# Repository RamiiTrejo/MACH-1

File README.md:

# Mach-1
Proyecto de robot seguidor de línea de alta velocidad, orientado a competencias de Line Follower Racing (LNR). Está diseñado para la categoría profesional, incorporando soluciones avanzadas como un sistema de succión que mejora la adherencia y el rendimiento en pista.

# Objetivos
Desarrollar un vehículo autónomo capaz de detectar y seguir una trayectoria con alta precisión y velocidad, optimizando tanto el hardware como el software para lograr un desempeño competitivo.

# Componentes
- ATMEGA238P, AU
- TA6586
- MOTOR CORELESS 8520
- TURBINA CON MOTOR CORELESS 716
- REGLETA QTR8A
- BATERÍA 2 350mAh~450mAh

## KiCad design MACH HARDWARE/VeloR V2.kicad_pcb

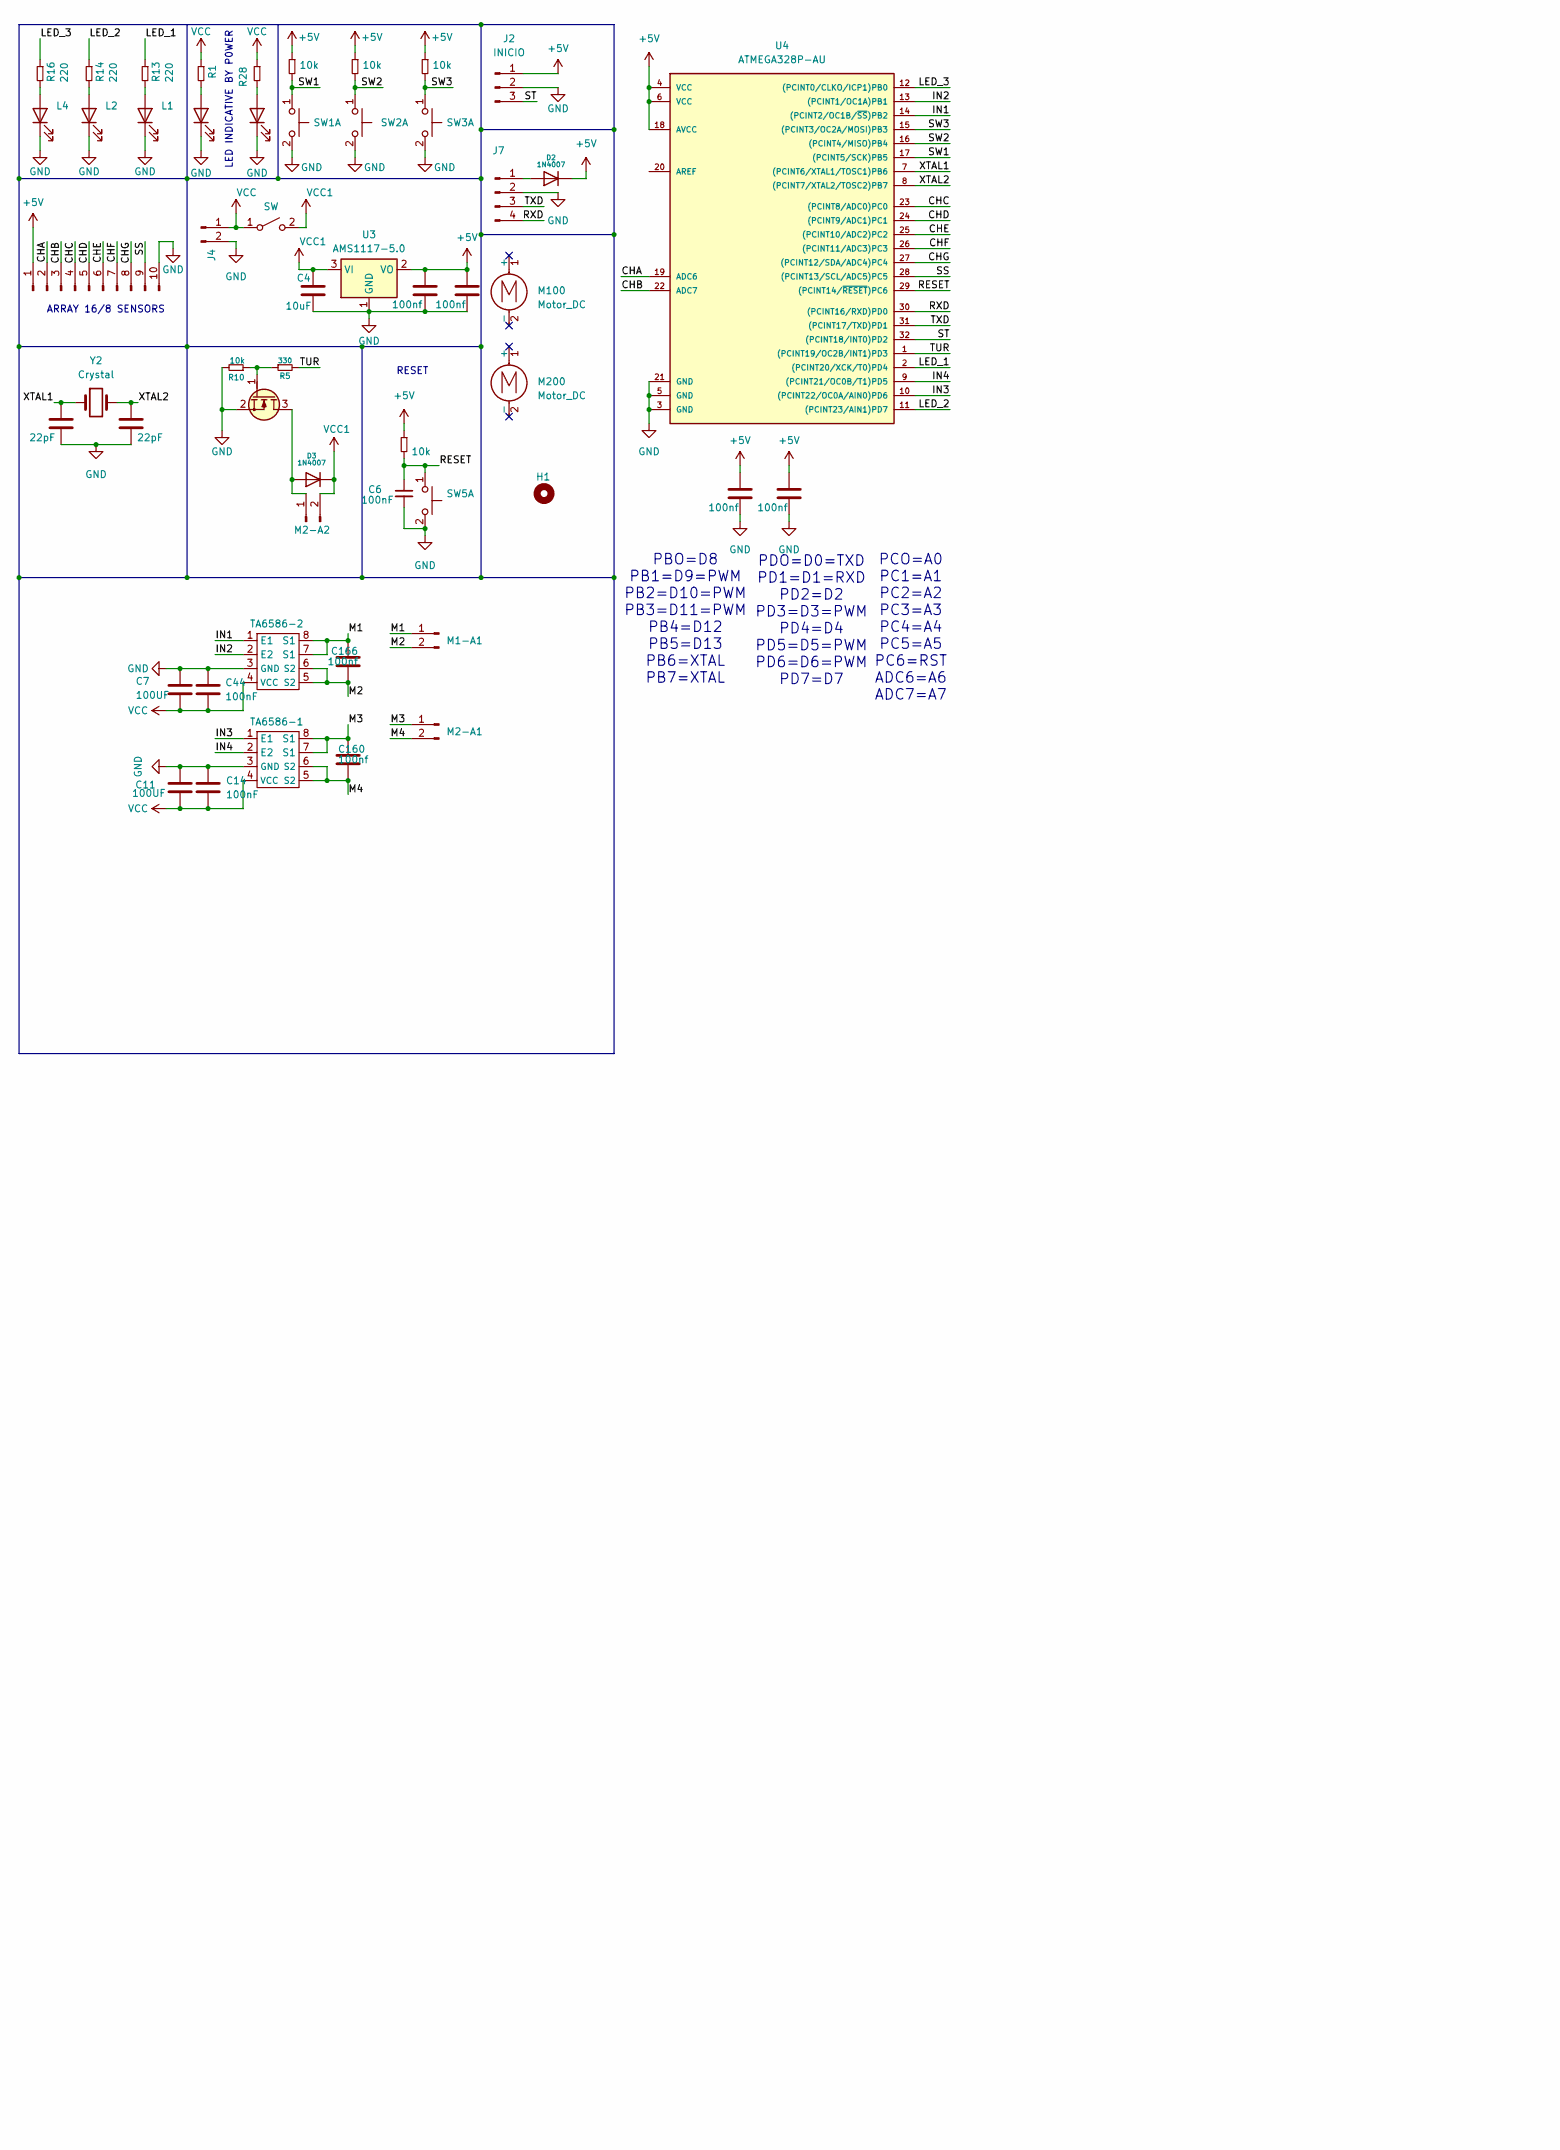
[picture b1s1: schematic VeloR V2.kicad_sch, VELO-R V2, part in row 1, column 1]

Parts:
C1, C2, C3, C15, C160, C166: 100nf; C_0805_2012Metric_Pad1.18x1.45mm_HandSolder
C4: 10uF; C_1206_3216Metric_Pad1.33x1.80mm_HandSolder
C5, C9: 22pF; C_0805_2012Metric_Pad1.18x1.45mm_HandSolder
C6, C14, C44: 100nF; C_0805_2012Metric_Pad1.18x1.45mm_HandSolder
C7, C11: 100UF; CP_EIA-7343-20_Kemet-V
D1, D11: LED; LED_0805_2012Metric_Pad1.15x1.40mm_HandSolder
D2, D3: 1N4007; D_SMA
H1: MountingHole; TURBINA
J2: INICIO; PinHeader_1x03_P2.54mm_Vertical
J3: Conn_01x10_Pin; JST_XH_S10B-XH-A_1x10_P2.50mm_Horizontal
J4: Conn_01x02_Pin; JST_XH_B3B-XH-A_1x03_P2.50mm_Vertical
J7: Conn_01x04_Pin; PinHeader_1x04_P2.54mm_Horizontal
L1, L2, L4: LED; LED_0805_2012Metric_Pad1.15x1.40mm_HandSolder
M1-A1, M2-A1, M2-A2: Conn_01x02_Pin; Hirose_DF13-02P-1.25DSA_1x02_P1.25mm_Vertical
M100, M200: Motor_DC; Coreless motor
Q1: AO3400A; SOT-23
R1, R28: 1K; R_1206_3216Metric_Pad1.30x1.75mm_HandSolder
R2, R3, R4, R6: 10k; R_1206_3216Metric_Pad1.30x1.75mm_HandSolder
R5: 330; R_0805_2012Metric_Pad1.20x1.40mm_HandSolder
R10: 10k; R_0805_2012Metric_Pad1.20x1.40mm_HandSolder
R13, R14, R16: 220; R_1206_3216Metric_Pad1.30x1.75mm_HandSolder
SW1, SW2, SW3, SW5: SW_Push_Dual_x2; SW SMD 3.5X6X5
SW6: SW; PinHeader_1x03_P2.54mm_Vertical
TA6586-1, TA6586-2: DIP-8_W7.62mm
U3: AMS1117-5.0; SOT-223-3_TabPin2
U4: ATMEGA328P-AU; TQFP-32_7x7mm_P0.8mm
Y2: Crystal; Crystal_HC49-4H_Vertical

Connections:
+5V: C1.1, C2.1, C3.1, C15.1, D2.1 (K), J2.1, J3.1, R2.1, R3.1, R4.1, R6.1, U3.2 (VO), U4.4 (VCC), U4.6 (VCC), U4.18 (AVCC)
/CHA: J3.2, U4.19 (ADC6)
/CHB: J3.3, U4.22 (ADC7)
/CHC: J3.4, U4.23 ((PCINT8/ADC0)PC0)
/CHD: J3.5, U4.24 ((PCINT9/ADC1)PC1)
/CHE: J3.6, U4.25 ((PCINT10/ADC2)PC2)
/CHF: J3.7, U4.26 ((PCINT11/ADC3)PC3)
/CHG: J3.8, U4.27 ((PCINT12/SDA/ADC4)PC4)
/IN1: TA6586-2.1 (E1), U4.14 ((PCINT2/OC1B/~SS)PB2)
/IN2: TA6586-2.2 (E2), U4.13 ((PCINT1/OC1A)PB1)
/IN3: TA6586-1.1 (E1), U4.10 ((PCINT22/OC0A/AIN0)PD6)
/IN4: TA6586-1.2 (E2), U4.9 ((PCINT21/OC0B/T1)PD5)
/LED_1: R13.1, U4.2 ((PCINT20/XCK/T0)PD4)
/LED_2: R14.1, U4.11 ((PCINT23/AIN1)PD7)
/LED_3: R16.1, U4.12 ((PCINT0/CLKO/ICP1)PB0)
/M1: C166.1, M1-A1.1, TA6586-2.7 (S1), TA6586-2.8 (S1)
/M2: C166.2, M1-A1.2, TA6586-2.5 (S2), TA6586-2.6 (S2)
/M3: C160.1, M2-A1.1, TA6586-1.7 (S1), TA6586-1.8 (S1)
/M4: C160.2, M2-A1.2, TA6586-1.5 (S2), TA6586-1.6 (S2)
/RESET: C6.1, R6.2, SW5.1 (C), U4.29 ((PCINT14/~RESET)PC6)
/RXD: J7.4, U4.30 ((PCINT16/RXD)PD0)
/SS: J3.9, U4.28 ((PCINT13/SCL/ADC5)PC5)
/ST: J2.3, U4.32 ((PCINT18/INT0)PD2)
/SW1: R2.2, SW1.1 (C), U4.17 ((PCINT5/SCK)PB5)
/SW2: R3.2, SW2.1 (C), U4.16 ((PCINT4/MISO)PB4)
/SW3: R4.2, SW3.1 (C), U4.15 ((PCINT3/OC2A/MOSI)PB3)
/TUR: R5.2, U4.1 ((PCINT19/OC2B/INT1)PD3)
/TXD: J7.3, U4.31 ((PCINT17/TXD)PD1)
/XTAL1: C5.1, U4.7 ((PCINT6/XTAL1/TOSC1)PB6), Y2.1
/XTAL2: C9.1, U4.8 ((PCINT7/XTAL2/TOSC2)PB7), Y2.2
GND: C1.2, C2.2, C3.2, C4.2, C5.2, C6.2, C7.1, C9.2, C11.1, C14.1, C15.2, C44.1, D1.1 (K), D11.1 (K), J2.2, J3.10, J4.2, J7.2, L1.1 (K), L2.1 (K), L4.1 (K), Q1.2 (S), R10.2, SW1.2 (D), SW2.2 (D), SW3.2 (D), SW5.2 (D), TA6586-1.3 (GND), TA6586-2.3 (GND), U3.1 (GND), U4.3 (GND), U4.5 (GND), U4.21 (GND)
unnamed: D1.2 (A), R1.2
unnamed: D2.2 (A), J7.1
unnamed: D3.2 (A), M2-A2.1, Q1.3 (D)
unnamed: D11.2 (A), R28.2
unnamed: L1.2 (A), R13.2
unnamed: L2.2 (A), R14.2
unnamed: L4.2 (A), R16.2
unnamed: Q1.1 (G), R5.1, R10.1
VCC: C7.2, C11.2, C14.2, C44.2, J4.1, R1.1, R28.1, SW6.1 (A), TA6586-1.4 (VCC), TA6586-2.4 (VCC)
VCC1: C4.1, D3.1 (K), M2-A2.2, SW6.2 (B), U3.3 (VI)

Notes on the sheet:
PCO=A0 PC1=A1 PC2=A2 PC3=A3 PC4=A4 PC5=A5 PC6=RST ADC6=A6 ADC7=A7
LED INDICATIVE BY P0WER
PBO=D8 PB1=D9=PWM PB2=D10=PWM PB3=D11=PWM PB4=D12 PB5=D13 PB6=XTAL PB7=XTAL
ARRAY 16/8 SENSORS
RESET
PDO=D0=TXD PD1=D1=RXD PD2=D2 PD3=D3=PWM PD4=D4 PD5=D5=PWM PD6=D6=PWM PD7=D7

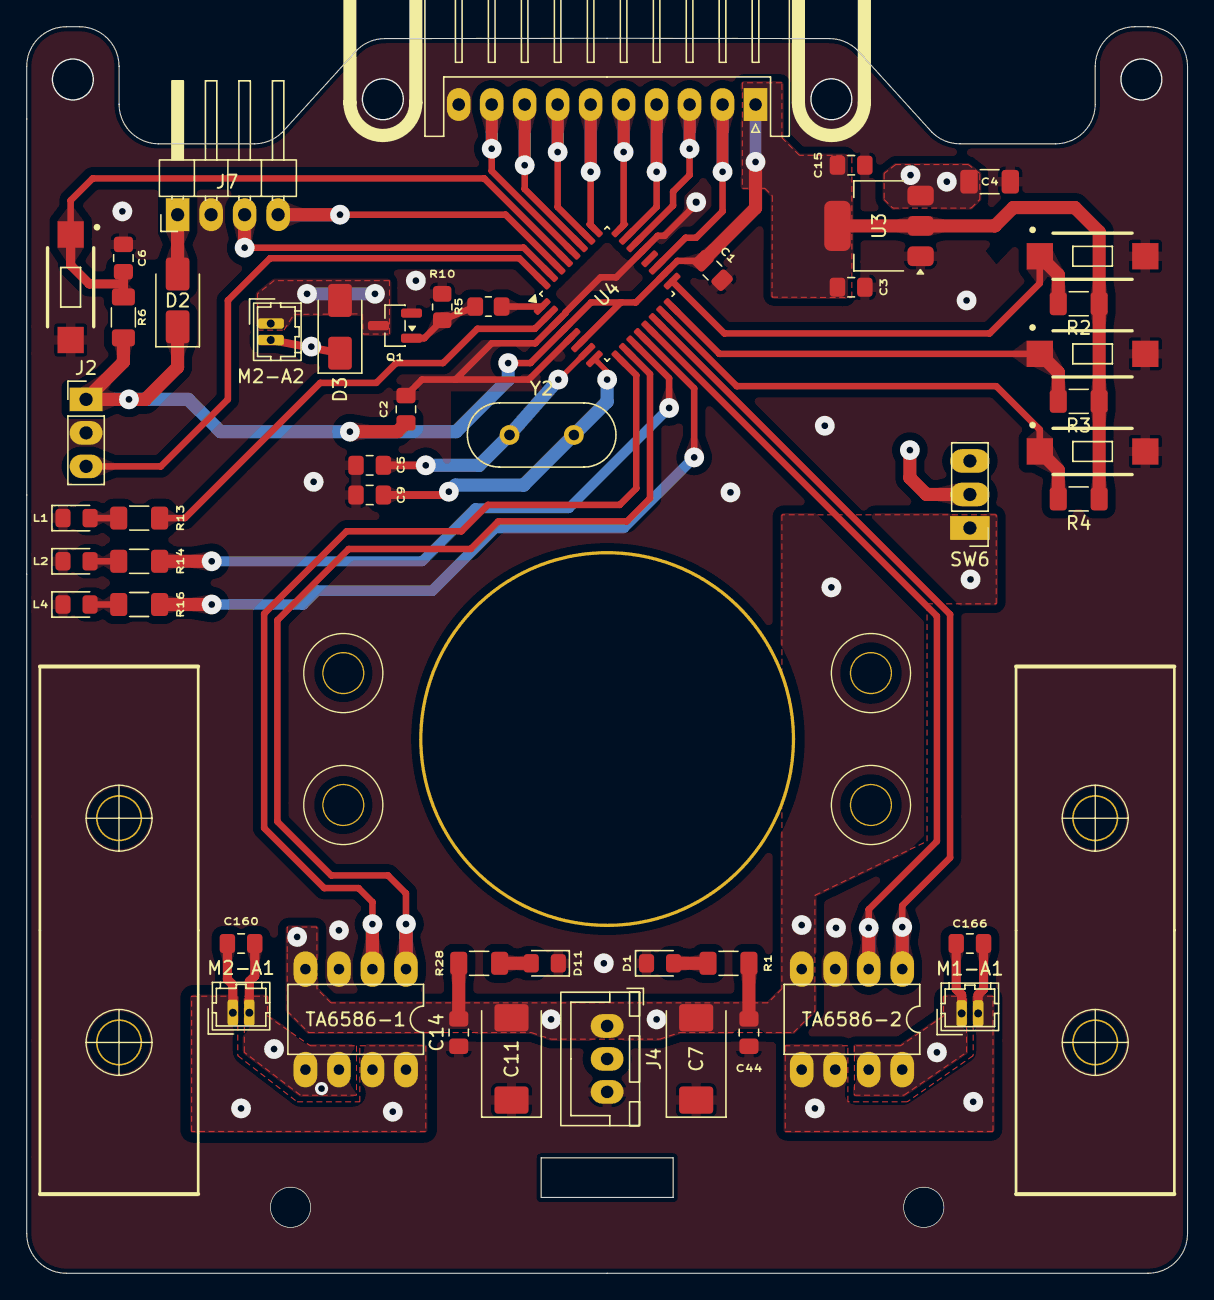
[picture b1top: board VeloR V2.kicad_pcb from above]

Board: 2 copper layers, 88.0 x 94.5 mm, 53 parts (0 on the bottom side), 41 nets.

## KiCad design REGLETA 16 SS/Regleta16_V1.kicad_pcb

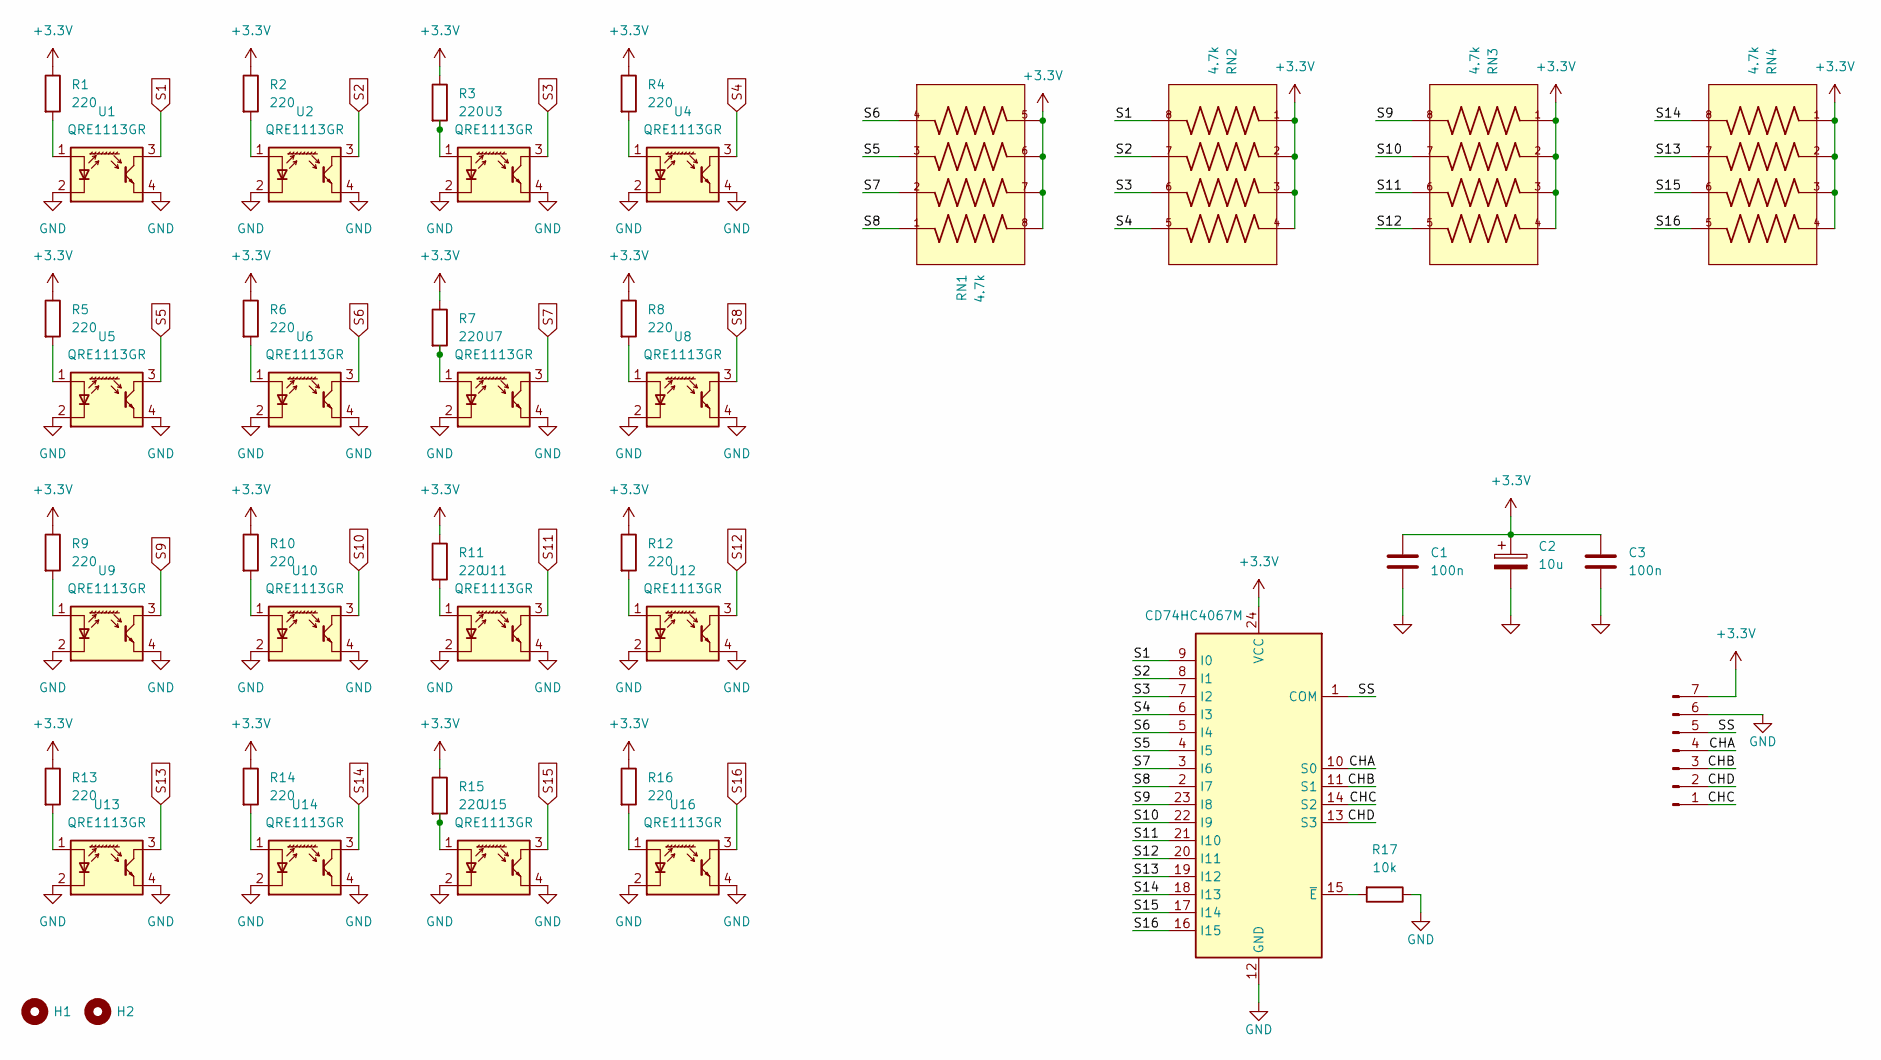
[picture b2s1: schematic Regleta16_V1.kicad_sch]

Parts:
C1, C3: 100n; C_0805_2012Metric_Pad1.18x1.45mm_HandSolder
C2: 10u; C_1206_3216Metric_Pad1.33x1.80mm_HandSolder
H1, H2: Mounting_Hole; MountingHole_3.2mm_M3
J1: Conn_01x07_Pin; JST_XH_S7B-XH-A_1x07_P2.50mm_Horizontal
R1, R2, R3, R4, R5, R6, R7, R8, R9, R10, R11, R12, R13, R14, R15, R16: 220; R_1206_3216Metric_Pad1.30x1.75mm_HandSolder
R17: 10k; R_1206_3216Metric_Pad1.30x1.75mm_HandSolder
RN1, RN2, RN3, RN4: 4.7k; R_Array_Convex_4x1206
U1, U2, U3, U4, U5, U6, U7, U8, U9, U10, U11, U12, U13, U14, U15, U16: QRE1113GR; OnSemi_CASE100CY
U18: CD74HC4067M; SOIC-24W_7.5x15.4mm_P1.27mm

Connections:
+3.3V: C1.1, C2.1, C3.1, J1.7, R1.1, R2.1, R3.1, R4.1, R5.1, R6.1, R7.1, R8.1, R9.1, R10.1, R11.1, R12.1, R13.1, R14.1, R15.1, R16.1, RN1.5, RN1.6, RN1.7, RN1.8, RN2.1, RN2.2, RN2.3, RN2.4, RN3.1, RN3.2, RN3.3, RN3.4, RN4.1, RN4.2, RN4.3, RN4.4, U18.24 (VCC)
/CHA: J1.4, U18.10 (S0)
/CHB: J1.3, U18.11 (S1)
/CHC: J1.1, U18.14 (S2)
/CHD: J1.2, U18.13 (S3)
/SS: J1.5, U18.1 (COM)
GND: C1.2, C2.2, C3.2, J1.6, R17.1, U1.2 (K), U1.4, U2.2 (K), U2.4, U3.2 (K), U3.4, U4.2 (K), U4.4, U5.2 (K), U5.4, U6.2 (K), U6.4, U7.2 (K), U7.4, U8.2 (K), U8.4, U9.2 (K), U9.4, U10.2 (K), U10.4, U11.2 (K), U11.4, U12.2 (K), U12.4, U13.2 (K), U13.4, U14.2 (K), U14.4, U15.2 (K), U15.4, U16.2 (K), U16.4, U18.12 (GND)
unnamed: R1.2, U1.1 (A)
unnamed: R2.2, U2.1 (A)
unnamed: R3.2, U3.1 (A)
unnamed: R4.2, U4.1 (A)
unnamed: R5.2, U5.1 (A)
unnamed: R6.2, U6.1 (A)
unnamed: R7.2, U7.1 (A)
unnamed: R8.2, U8.1 (A)
unnamed: R9.2, U9.1 (A)
unnamed: R10.2, U10.1 (A)
unnamed: R11.2, U11.1 (A)
unnamed: R12.2, U12.1 (A)
unnamed: R13.2, U13.1 (A)
unnamed: R14.2, U14.1 (A)
unnamed: R15.2, U15.1 (A)
unnamed: R16.2, U16.1 (A)
unnamed: R17.2, U18.15 (~E)
S1: RN2.8, U1.3, U18.9 (I0)
S2: RN2.7, U2.3, U18.8 (I1)
S3: RN2.6, U3.3, U18.7 (I2)
S4: RN2.5, U4.3, U18.6 (I3)
S5: RN1.3, U5.3, U18.4 (I5)
S6: RN1.4, U6.3, U18.5 (I4)
S7: RN1.2, U7.3, U18.3 (I6)
S8: RN1.1, U8.3, U18.2 (I7)
S9: RN3.8, U9.3, U18.23 (I8)
S10: RN3.7, U10.3, U18.22 (I9)
S11: RN3.6, U11.3, U18.21 (I10)
S12: RN3.5, U12.3, U18.20 (I11)
S13: RN4.7, U13.3, U18.19 (I12)
S14: RN4.8, U14.3, U18.18 (I13)
S15: RN4.6, U15.3, U18.17 (I14)
S16: RN4.5, U16.3, U18.16 (I15)

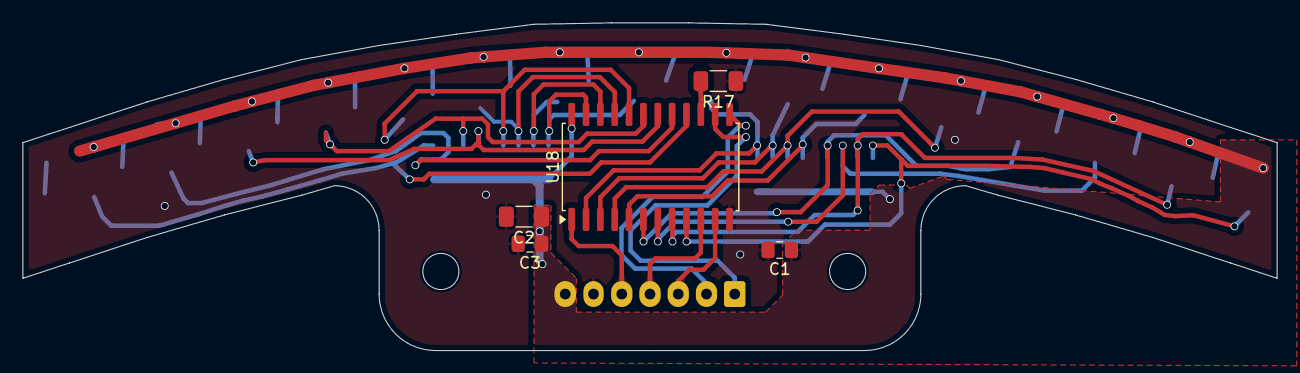
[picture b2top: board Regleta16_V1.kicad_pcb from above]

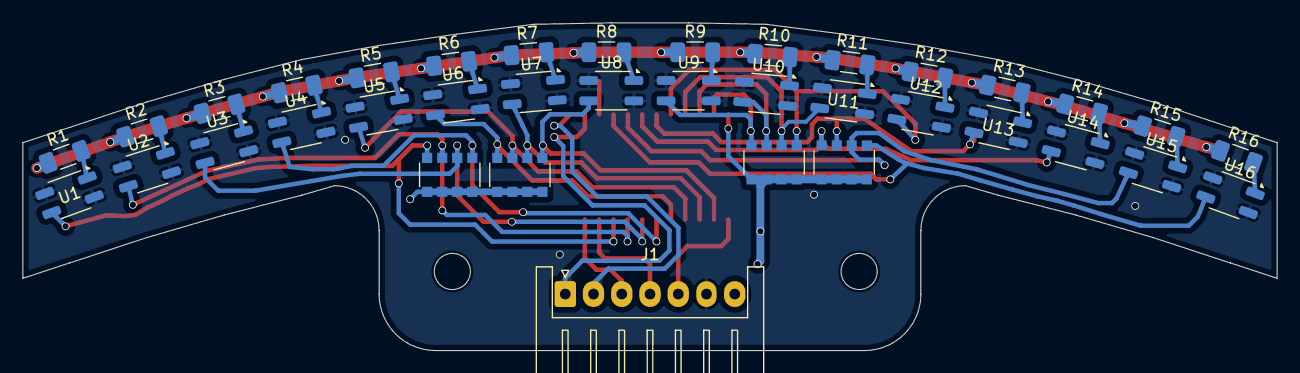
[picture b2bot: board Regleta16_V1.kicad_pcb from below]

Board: 2 copper layers, 111.0 x 29.0 mm, 44 parts (37 on the bottom side), 40 nets.

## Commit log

2026-03-18 Mi primer
2026-03-18 modificamos titulo en index.html
2026-03-27 Create SOFTWARE
2026-04-03 Update SOFTWARE
2026-05-02 Add files via upload
    MACH, TRUBINE, DRIVERS TA6586, CNC MACHINE
2026-05-02 Add battery specifications to README
